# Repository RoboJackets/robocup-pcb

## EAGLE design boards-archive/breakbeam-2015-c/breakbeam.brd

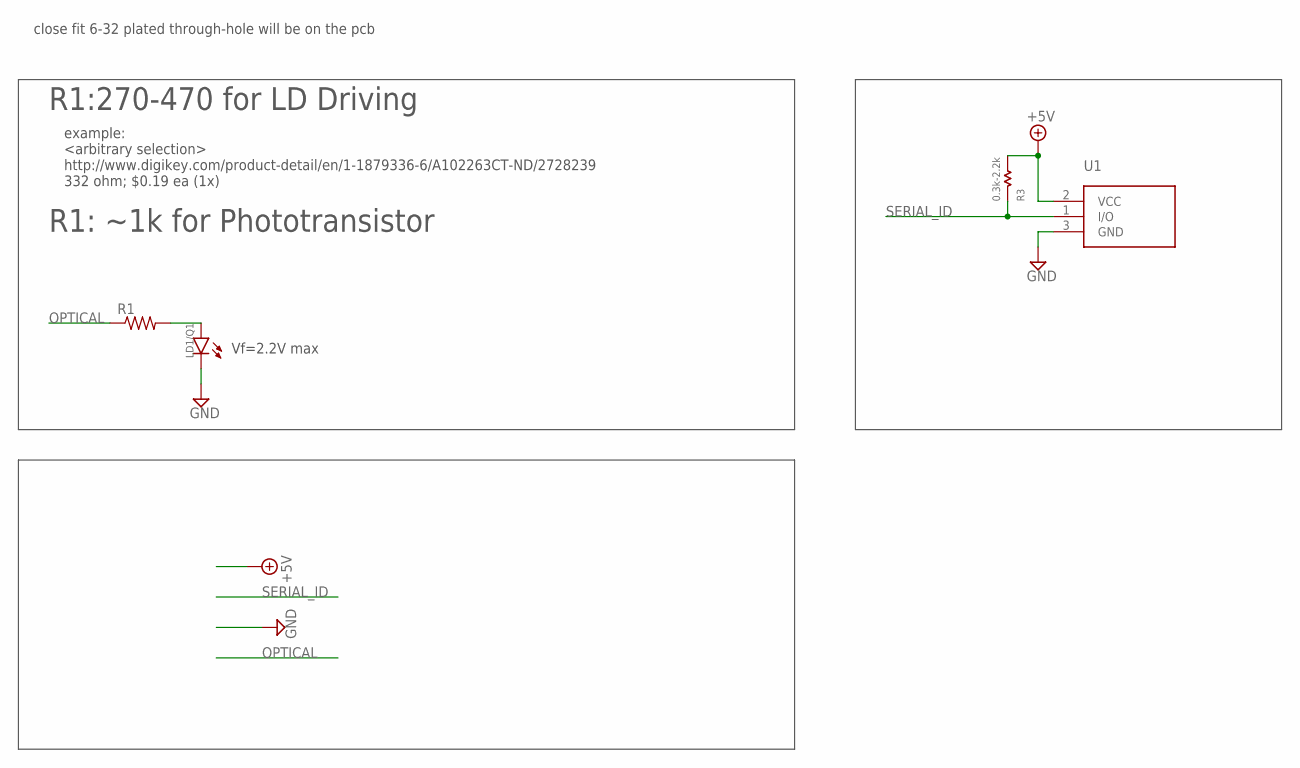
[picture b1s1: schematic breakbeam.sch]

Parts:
LD1/Q1: LD_SIDELOOK_FACEDOWNEXTRA_SHORT_LEAD_MINIMIZED; 2LEAD_H_FACEDOWN_XSHORT_MIN
R1: R-US_R0603; R0603
R3: 0.3k-2.2k; GHOST_0.075
U1: DS2411; SOT-23-3

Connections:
+5V: R3.P$2 (PIN2), U1.2 (VCC)
GND: LD1/Q1.1 (C), U1.3 (GND)
unnamed: LD1/Q1.2 (A), R1.2
OPTICAL: R1.1
SERIAL_ID: R3.P$1 (PIN1), U1.1 (I/O)

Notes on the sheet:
Vf=2.2V max
example: <arbitrary selection> http://www.digikey.com/product-detail/en/1-1879336-6/A102263CT-ND/2728239 332 ohm; $0.19 ea (1x)
close fit 6-32 plated through-hole will be on the pcb
R1:270-470 for LD Driving
R1: ~1k for Phototransistor

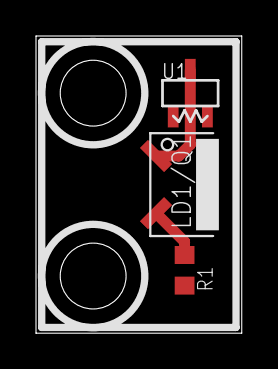
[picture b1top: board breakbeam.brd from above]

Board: 2 copper layers, 11.4 x 16.5 mm, 4 parts (0 on the bottom side), 4 nets.

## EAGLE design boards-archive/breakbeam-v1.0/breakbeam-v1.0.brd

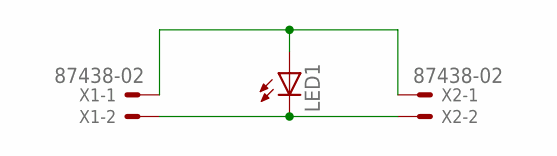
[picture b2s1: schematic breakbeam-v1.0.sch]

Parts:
LED1: LED3MM
X1, X2: 87438-02

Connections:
unnamed: LED1.A, X1.1, X2.1
unnamed: LED1.K (C), X1.2, X2.2

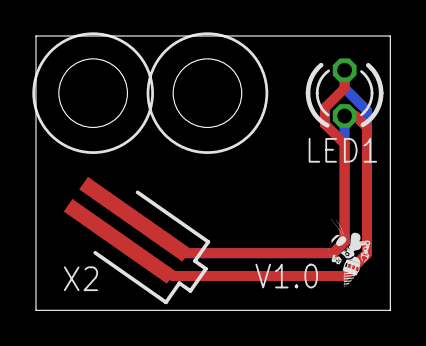
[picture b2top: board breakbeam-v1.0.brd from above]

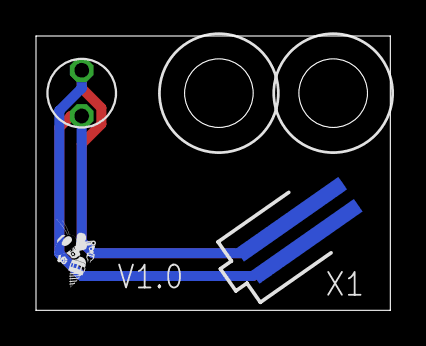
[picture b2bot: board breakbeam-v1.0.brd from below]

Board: 2 copper layers, 19.7 x 15.2 mm, 5 parts (2 on the bottom side), 2 nets.

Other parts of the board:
U$1, U$4: ROBOBUZZ_0.2X

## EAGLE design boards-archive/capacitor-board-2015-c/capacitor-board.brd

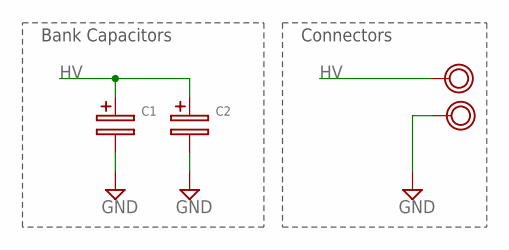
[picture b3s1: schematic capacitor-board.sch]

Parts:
C1, C2: RC_CAPHORIZ; 25MM-DIA_HORIZ
U$1, U$3: VIA_TP; VIA_2MM

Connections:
GND: C1.-, C2.-, U$3.P$1
HV: C1.+, C2.+, U$1.P$1

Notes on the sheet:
Bank Capacitors
Connectors

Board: 2 copper layers, 6 parts (1 on the bottom side), 2 nets, no tracks yet.

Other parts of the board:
U$2, U$4: ROBOBUZZ_0.4X

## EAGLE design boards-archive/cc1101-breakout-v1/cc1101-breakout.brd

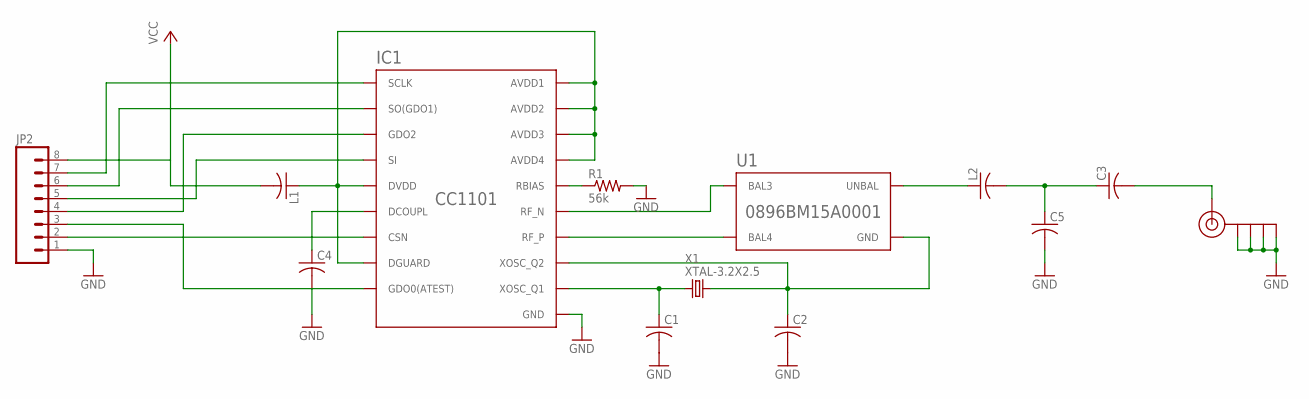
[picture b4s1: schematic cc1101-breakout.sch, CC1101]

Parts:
C1, C2, C3, C4: C-USC0603; C0603
C5: C-USC0402; C0402
IC1: CC1101; QLP20
J$1: SMA_EDGE; SMA-EDGE
JP2: M081X08; 1X08
L1: C-USC0603; C0603
L2: C-USC0402; C0402
R1: 56k; R0603
U1: 0896BM15A0001
X1: XTAL-3.2X2.5

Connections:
GND: C1.2, C2.2, C4.2, C5.2, IC1.16 (GND), IC1.19 (GND), IC1.GND, IC1.GND1 (GND), IC1.GND2 (GND), IC1.GND3 (GND), IC1.GND4 (GND), IC1.GND5 (GND), J$1.GND@0 (GND), J$1.GND@1 (GND), J$1.GND@2 (GND), J$1.GND@3 (GND), JP2.1, R1.2
unnamed: IC1.12 (RF_P), U1.4 (BAL4)
unnamed: IC1.13 (RF_N), U1.3 (BAL3)
unnamed: IC1.1 (SCLK), JP2.7
unnamed: C1.1, IC1.8 (XOSC_Q1), X1.1
unnamed: C2.1, IC1.10 (XOSC_Q2), U1.2 (GND), U1.5 (GND), U1.6 (GND), X1.3 (2)
unnamed: IC1.17 (RBIAS), R1.1
unnamed: IC1.2 (SO(GDO1)), JP2.6
unnamed: IC1.20 (SI), JP2.5
unnamed: L2.1, U1.1 (UNBAL)
unnamed: IC1.3 (GDO2), JP2.4
unnamed: IC1.6 (GDO0(ATEST)), JP2.3
unnamed: IC1.7 (CSN), JP2.2
unnamed: C4.1, IC1.5 (DCOUPL)
unnamed: C3.1, C5.1, L2.2
unnamed: C3.2, J$1.SIG (SIGNAL)
unnamed: IC1.4 (DVDD), IC1.9 (AVDD1), IC1.11 (AVDD2), IC1.14 (AVDD3), IC1.15 (AVDD4), IC1.18 (DGUARD), L1.1
VCC: JP2.8, L1.2

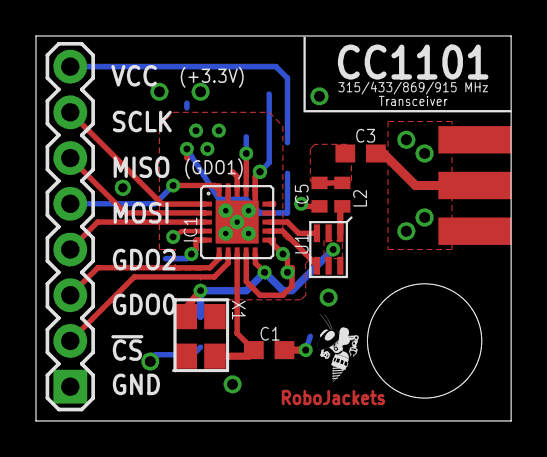
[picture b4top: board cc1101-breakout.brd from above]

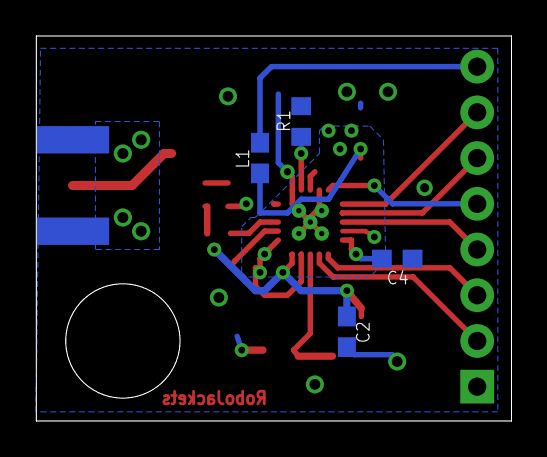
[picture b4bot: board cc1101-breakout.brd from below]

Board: 4 copper layers, 26.4 x 21.4 mm, 14 parts (4 on the bottom side), 18 nets.

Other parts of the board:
U$1: ROBOBUZZ_0.2X

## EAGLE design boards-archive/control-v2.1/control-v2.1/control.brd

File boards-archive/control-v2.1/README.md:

# Control Board

Board which contains micro-controller (MBED), power circuitry, FPGA, and all motor control circuitry.

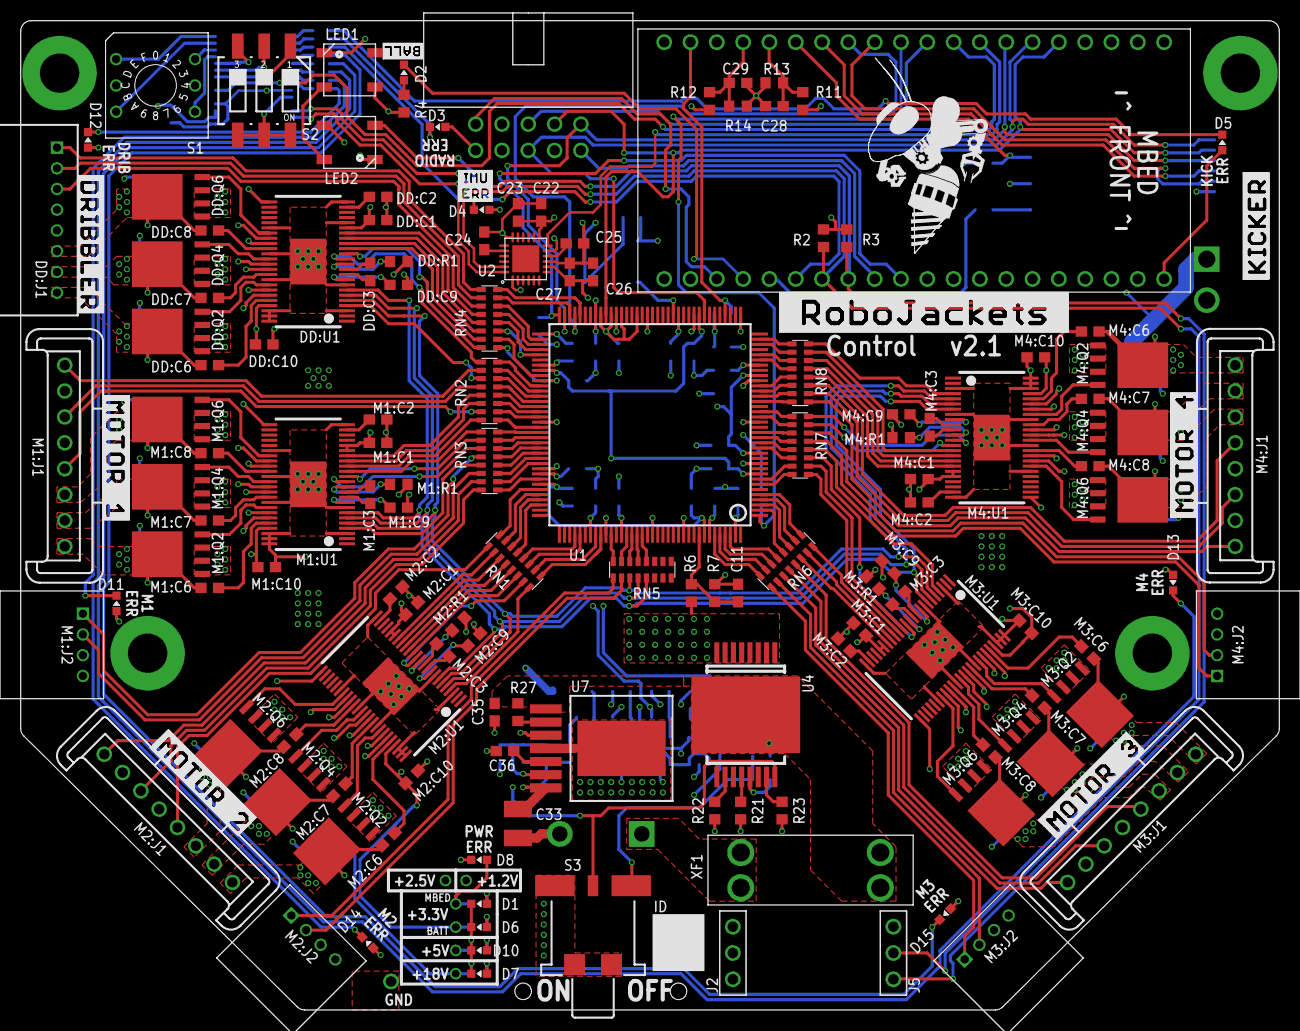
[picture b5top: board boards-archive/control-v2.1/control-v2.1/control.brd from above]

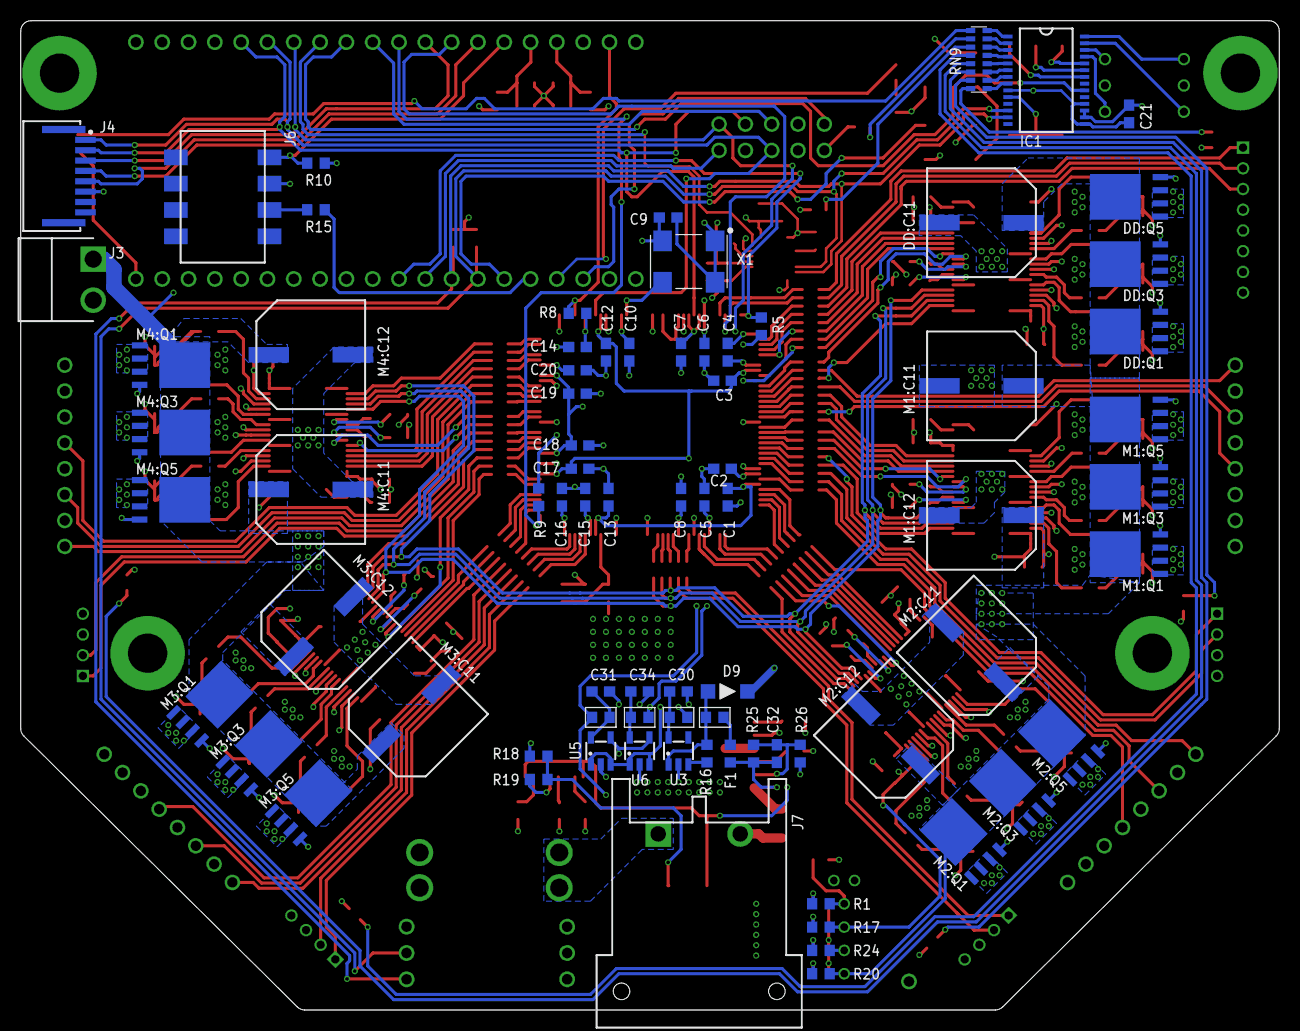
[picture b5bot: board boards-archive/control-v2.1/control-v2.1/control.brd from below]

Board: 4 copper layers, 121.5 x 95.5 mm, 223 parts (78 on the bottom side), 288 nets.

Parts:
C1, C2, C3, C4, C5, C6, C7, C8, C9, C10, C11, C12, C13, C14, C15, C16, C17, C18, C19, C20, C21, C25, C28, C29: 0.1uF; C0603
C22, C23, C27: 0.47uF; C0603
C24: 2200pF; C0603
C26: 10000pF; C0603
C30, C31, C34: 1uF; C0603
C32: 0.022uF; C0603
C33: LMK325ABJ107MM-P; C1210
C35: GRM188R6YA106MA73D; C0603
C36: 0.1uF 50V; C0603
D1, D6, D7, D10: GREEN; CHIP-LED0603
D2: BLUE; CHIP-LED0603
D3, D4, D5, D8, D11, D12, D13, D14, D15: RED; CHIP-LED0603
D9: SOD123
DD:C1, DD:C2: 1uF; C0603
DD:C3: 0.022uF 50V; C0603
DD:C6, DD:C7, DD:C8, DD:C10: 0.1uF 50V; C0603
DD:C9: 2.2uF 50V; C0603
DD:C11: UWZ1H221MCL1GS
DD:J1: 8-PIN_2MM-H; 2MM-8-H
DD:Q1, DD:Q2, DD:Q3, DD:Q4, DD:Q5, DD:Q6: IRFH7545; PQFN_5X6_E
DD:R1: 10k; R0603
DD:U1: DRV8303DCA; TSSOP-48_PAD
F1: 0603L075SLYR; F0603
IC1: MCP23017-E/SS; SSOP-28
J1: SBH11-PBPC-D05-RA; SBH11-*-D05-RA
J2, J5: 3-PIN-HEADER
J3: B2PS-VH(LF)(SN); B2PS-CENTERED
J4: HFW8R-1ST
J6: 147721-3
J7: DF22-2; DF22-2-H
KIT1: MBED_NXP_LPC1768; MBED-KIT
LED1, LED2: WS2812B; 5050
M1:C1, M1:C2, M2:C1, M2:C2, M3:C1, M3:C2, M4:C1, M4:C2: 1uF; C0603
M1:C3, M2:C3, M3:C3, M4:C3: 0.022uF 50V; C0603
M1:C6, M1:C7, M1:C8, M1:C10, M2:C6, M2:C7, M2:C8, M2:C10, M3:C6, M3:C7, M3:C8, M3:C10, M4:C6, M4:C7, M4:C8, M4:C10: 0.1uF 50V; C0603
M1:C9, M2:C9, M3:C9, M4:C9: 2.2uF 50V; C0603
M1:C11, M1:C12, M2:C11, M2:C12, M3:C11, M3:C12, M4:C11, M4:C12: UWZ1H221MCL1GS
M1:J1, M2:J1, M3:J1, M4:J1: MKS-1658
M1:J2, M2:J2, M3:J2, M4:J2: 4-PIN_2MM-H; 2MM-4-H
M1:Q1, M1:Q2, M1:Q3, M1:Q4, M1:Q5, M1:Q6, M2:Q1, M2:Q2, M2:Q3, M2:Q4, M2:Q5, M2:Q6, M3:Q1, M3:Q2, M3:Q3, M3:Q4, M3:Q5, M3:Q6, M4:Q1, M4:Q2, M4:Q3, M4:Q4, M4:Q5, M4:Q6: IRFH7545; PQFN_5X6_E
M1:R1, M2:R1, M3:R1, M4:R1: 10k; R0603
M1:U1, M2:U1, M3:U1, M4:U1: DRV8303DCA; TSSOP-48_PAD
R1, R4, R5, R15, R17: 330; R0603
R2, R3, R8, R9: 4.7k; R0603
R6, R11: 68k; R0603
R7, R10, R12, R13, R14, R16, R21: 10k; R0603
R18: 270k; R0603
R19, R27: 100k; R0603
R20, R22, R23, R24: 1k; R0603
R25: 34k; R0603
R26: 6.49k; R0603
RN1, RN2, RN3, RN4, RN5, RN6, RN7, RN8, RN9: 330; RA-8_2506
S1: 94HCB16T; HEX
S2: 219-03; CTS-219-03
S3: 34EWMSP12M6RT
SB1, SB2, SB3, SB4: SOLDERBRIDGESB0603; SB0603
U1: XC3S250E-4TQG144C; TQFP144
U2: MPU-6050; QFN-24-4MM2
U3: TLV70233DBVR; SOT-23-5
U4: VND5E006ASPTR-E; POWERSO-16
U5: MCP1824T-1202E/OT; SOT-23-5
U6: MCP1824T-2502E/OT; SOT-23-5
U7: LMZ14201; TO-PMOD-7
U$2: ROBOJACKETS
U$3: MOTOR-1
U$4: DRIBBLER
U$5: MOTOR-2
U$6: MOTOR-3
U$7: MOTOR-4
U$8: BALL
U$9: KICKER
U$10: ERR-IMU
U$11: ROBOBUZZ_1.0X2
X1: ASV-18.432MHZ-EJ-T; ASV
XF1: 30A; 3557-2

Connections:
3.3V-EN: R16.1, U3.3
3V3-LED: D6.A, R17.1
5V-LED: D10.A, R24.2
18.5V-LED: D7.A, R20.1
!CS!-FPGA: KIT1.P$13, U1.69
!CS!-KICK: J4.4, KIT1.P$14
!CS!-RADIO: J1.10, KIT1.P$29
!RST!-KICK: J4.5, KIT1.P$12
!RST!-RADIO: J1.5, KIT1.P$23
+1.2V: C3.1, C5.1, C12.1, C17.1, SB2.2, U1.9, U1.45, U1.80, U1.115
+1.2V-PRE: C31.1, SB2.1, U5.5
+2.5V: C1.1, C6.1, C13.1, C20.1, R5.2, R9.2, SB4.2, U1.30, U1.65, U1.102, U1.137
+2.5V-PRE: C34.1, SB4.1, U6.5
+3.3V: C2.1, C4.1, C7.1, C8.1, C9.1, C10.1, C14.1, C15.1, C16.1, C18.1, C19.1, C21.1, C22.1, C23.1, C26.1, C27.1, D3.A, D4.A, D5.A, D8.A, D11.A, D12.A, D13.A, D14.A, D15.A, DD:J1.5, IC1.9, IC1.15, IC1.18, J1.6, J2.2, KIT1.VOUT, LED1.1, LED2.1, R1.1, R2.2, R3.2, R4.2, R8.1, R10.2, U1.13, U1.28, U1.42, U1.49, U1.57, U1.60, U1.62, U1.64, U1.79, U1.100, U1.121, U1.138, U1.143, U2.8, U2.13, U5.1, U5.3, U6.1, U6.3, X1.1, X1.4
+3.3V-LED: D1.A, R1.2
+3V3: DD:C1.1, DD:C10.1, DD:R1.1, DD:U1.19, DD:U1.45, M1:C1.1, M1:C10.1, M1:R1.1, M1:U1.19, M1:U1.20, M1:U1.45, M2:C1.1, M2:C10.1, M2:R1.1, M2:U1.19, M2:U1.20, M2:U1.45, M3:C1.1, M3:C10.1, M3:R1.1, M3:U1.19, M3:U1.20, M3:U1.45, M4:C1.1, M4:C10.1, M4:R1.1, M4:U1.19, M4:U1.20, M4:U1.45, R17.2, SB1.2
+3V3-PRE: C30.1, SB1.1, U3.5
+5V: D9.C, KIT1.VIN, KIT1.VU, M1:J1.4, M1:J2.4, M2:J1.4, M2:J2.4, M3:J1.4, M3:J2.4, M4:J1.4, M4:J2.4, R12.1, R24.1
+5V-FUSE: C32.1, C33.1, F1.1, R25.2, U7.7
+5V-PRE: D9.A, R16.2, SB3.2, U3.1
+5V-PRE2: F1.2, SB3.1
+18.5V: DD:C11.1, DD:Q1.5678, DD:Q3.5678, DD:Q5.5678, DD:U1.25, J3.1, M1:C11.1, M1:C12.1, M1:Q1.5678, M1:Q3.5678, M1:Q5.5678, M1:U1.25, M2:C11.1, M2:C12.1, M2:Q1.5678, M2:Q3.5678, M2:Q5.5678, M2:U1.25, M3:C11.1, M3:C12.1, M3:Q1.5678, M3:Q3.5678, M3:Q5.5678, M3:U1.25, M4:C11.1, M4:C12.1, M4:Q1.5678, M4:Q3.5678, M4:Q5.5678, M4:U1.25, R6.1, R11.1, R20.2, U4.1, U4.2, U4.3, U4.4, U4.5, U4.6, U4.7, U4.8
BALL-DETECT: J6.1, KIT1.P$15, R10.1
BALL-EMIT: KIT1.P$25, R15.2
BALL-EMIT-PRE: J6.3, R15.1
BATT-FPGA: C11.1, R6.2, R7.1, U1.136
CPOUT: C24.1, U2.20
CS1: R22.2, U4.10
CS2: R23.2, U4.15
CS-DIS: R21.2, U4.12
DD-!CS: DD:U1.4, RN2.11
DD-A-H: DD:U1.13, RN2.9
DD-A-L: DD:U1.14, RN4.16
DD-B-H: DD:U1.15, RN4.15
DD-B-L: DD:U1.16, RN4.14
DD-C-H: DD:U1.17, RN4.13
DD-C-L: DD:U1.18, RN4.12
DD-H1: DD:J1.3, RN4.11
DD-H2: DD:J1.2, RN4.10
DD-H3: DD:J1.1, RN4.9
DD:AVDD: DD:C2.1, DD:U1.23
DD:BST-A: DD:C6.1, DD:U1.44
DD:BST-B: DD:C7.1, DD:U1.39
DD:BST-C: DD:C8.1, DD:U1.34
DD:CP1: DD:C3.1, DD:U1.10
DD:CP2: DD:C3.2, DD:U1.11
DD:EN-GATE: DD:R1.2, DD:U1.12
DD:GH-A: DD:Q1.4, DD:U1.43
DD:GH-B: DD:Q3.4, DD:U1.38
DD:GH-C: DD:Q5.4, DD:U1.33
DD:GL-A: DD:Q2.4, DD:U1.41
DD:GL-B: DD:Q4.4, DD:U1.36
DD:GL-C: DD:Q6.4, DD:U1.31
DD:GVDD: DD:C9.1, DD:U1.9
DD:PHASE-A: DD:C6.2, DD:J1.8, DD:Q1.1, DD:Q1.2, DD:Q1.3, DD:Q2.5678, DD:U1.42
DD:PHASE-B: DD:C7.2, DD:J1.7, DD:Q3.1, DD:Q3.2, DD:Q3.3, DD:Q4.5678, DD:U1.37
DD:PHASE-C: DD:C8.2, DD:J1.6, DD:Q5.1, DD:Q5.2, DD:Q5.3, DD:Q6.5678, DD:U1.32
DIP-1: IC1.22, S2.1
DIP-2: IC1.23, S2.2
DIP-3: IC1.24, S2.3
EN-PWR: S3.2, U4.9, U4.16, U7.3
EN-PWR-PRE: R18.1, R19.2, S3.1
FB: C32.2, R25.1, R26.2, U7.6
FPGA-CLK: U1.50, X1.3
FPGA-DONE: KIT1.P$30, R5.1, U1.72
FPGA-INIT: KIT1.P$19, R8.2, U1.40
FPGA-PROG: KIT1.P$11, R9.1, U1.1
GND: C1.2, C2.2, C3.2, C4.2, C5.2, C6.2, C7.2, C8.2, C9.2, C10.2, C11.2, C12.2, C13.2, C14.2, C15.2, C16.2, C17.2, C18.2, C19.2, C20.2, C21.2, C22.2, C23.2, C24.2, C25.2, C26.2, C27.2, C28.2, C29.2, C30.2, C31.2, C33.2, C34.2, C35.2, C36.2, D1.C, D6.C, D7.C, D10.C, DD:C1.2, DD:C2.2, DD:C9.2, DD:C10.2, DD:C11.2, DD:J1.4, DD:Q2.1, DD:Q2.2, DD:Q2.3, DD:Q4.1, DD:Q4.2, DD:Q4.3, DD:Q6.1, DD:Q6.2, DD:Q6.3, DD:U1.3, DD:U1.8, DD:U1.20, DD:U1.24, DD:U1.30, DD:U1.35, DD:U1.40, DD:U1.46, DD:U1.47, DD:U1.48, DD:U1.PAD, IC1.10, IC1.16, IC1.17, J1.7, J2.1, J3.2, J4.6, J6.2, J7.2, KIT1.GND, LED1.3, LED2.3, M1:C1.2, M1:C2.2, M1:C9.2, M1:C10.2, M1:C11.2, M1:C12.2, M1:J1.2, M1:J2.3, M1:Q2.1, M1:Q2.2, M1:Q2.3, M1:Q4.1, M1:Q4.2, M1:Q4.3, M1:Q6.1, M1:Q6.2, M1:Q6.3, M1:U1.3, M1:U1.8, M1:U1.24, M1:U1.30, M1:U1.35, M1:U1.40, M1:U1.46, M1:U1.47, M1:U1.48, M1:U1.PAD, M2:C1.2, M2:C2.2, M2:C9.2, M2:C10.2, M2:C11.2, M2:C12.2, M2:J1.2, M2:J2.3, M2:Q2.1, M2:Q2.2, M2:Q2.3, M2:Q4.1, M2:Q4.2, M2:Q4.3, M2:Q6.1, M2:Q6.2, M2:Q6.3, M2:U1.3, M2:U1.8, M2:U1.24, M2:U1.30, M2:U1.35, M2:U1.40, M2:U1.46, M2:U1.47, M2:U1.48, M2:U1.PAD, M3:C1.2, M3:C2.2, M3:C9.2, M3:C10.2, M3:C11.2, M3:C12.2, M3:J1.2, M3:J2.3, M3:Q2.1, M3:Q2.2, M3:Q2.3, M3:Q4.1, M3:Q4.2, M3:Q4.3, M3:Q6.1, M3:Q6.2, M3:Q6.3, M3:U1.3, M3:U1.8, M3:U1.24, M3:U1.30, M3:U1.35, M3:U1.40, M3:U1.46, M3:U1.47, M3:U1.48, M3:U1.PAD, M4:C1.2, M4:C2.2, M4:C9.2, M4:C10.2, M4:C11.2, M4:C12.2, M4:J1.2, M4:J2.3, M4:Q2.1, M4:Q2.2, M4:Q2.3, M4:Q4.1, M4:Q4.2, M4:Q4.3, M4:Q6.1, M4:Q6.2, M4:Q6.3, M4:U1.3, M4:U1.8, M4:U1.24, M4:U1.30, M4:U1.35, M4:U1.40, M4:U1.46, M4:U1.47, M4:U1.48, M4:U1.PAD, R7.2, R13.2, R14.2, R19.1, R21.1, R22.1, R23.1, R26.1, S1.C1, S1.C2, S2.4, S2.5, S2.6, S3.3, S3.LEG1, S3.LEG3, U1.11, U1.19, U1.27, U1.37, U1.46, U1.55, U1.61, U1.73, U1.90, U1.99, U1.118, U1.127, U1.133, U2.1, U2.9, U2.11, U2.18, U3.2, U4.13, U5.2, U6.2, U7.4, U7.PAD, X1.2
GPB0: IC1.1, RN9.8
GPB1: IC1.2, RN9.7
GPB2: IC1.3, RN9.6
GPB3: IC1.4, RN9.5
GPB4: IC1.5, RN9.4
GPB5: IC1.6, RN9.3
GPB6: IC1.7, RN9.2
GPB7: IC1.8, RN9.1
HEX-0: IC1.28, S1.1
HEX-1: IC1.25, S1.2
HEX-2: IC1.27, S1.4
HEX-3: IC1.26, S1.8
INT-IO: IC1.20, KIT1.P$9
INT-MPU: KIT1.P$8, U2.12
INT-RADIO: J1.3, KIT1.P$10
LED-BALL: D2.C, KIT1.P$24
LED-BALL-PRE: D2.A, R4.1
LED-DD: D12.C, RN9.16
LED-KICK: D5.C, RN9.9
LED-M1: D11.C, RN9.15
LED-M2: D14.C, RN9.14
LED-M3: D15.C, RN9.12
LED-M4: D13.C, RN9.13
LED-MPU: D4.C, RN9.11
LED-NEO: KIT1.P$26, LED2.4
LED-RADIO: D3.C, RN9.10
M1-!CS: M1:U1.4, RN3.13
M1-A-H: M1:U1.15, RN3.9
M1-A-L: M1:U1.16, RN2.16
M1-B-H: M1:U1.13, RN3.11
M1-B-L: M1:U1.14, RN3.10
M1-C-H: M1:U1.17, RN2.14
M1-C-L: M1:U1.18, RN2.13
M1-ENC-A: M1:J2.2, RN3.14
M1-ENC-B: M1:J2.1, RN3.12
M1-H1: M1:J1.1, RN2.10
M1-H2: M1:J1.3, RN2.12
M1-H3: M1:J1.5, RN2.15
M1:AVDD: M1:C2.1, M1:U1.23
M1:BST-A: M1:C6.1, M1:U1.44
M1:BST-B: M1:C7.1, M1:U1.39
M1:BST-C: M1:C8.1, M1:U1.34
M1:CP1: M1:C3.1, M1:U1.10
M1:CP2: M1:C3.2, M1:U1.11
M1:EN-GATE: M1:R1.2, M1:U1.12
M1:GH-A: M1:Q1.4, M1:U1.43
M1:GH-B: M1:Q3.4, M1:U1.38
M1:GH-C: M1:Q5.4, M1:U1.33
M1:GL-A: M1:Q2.4, M1:U1.41
M1:GL-B: M1:Q4.4, M1:U1.36
M1:GL-C: M1:Q6.4, M1:U1.31
M1:GVDD: M1:C9.1, M1:U1.9
M1:PHASE-A: M1:C7.2, M1:J1.7, M1:Q3.1, M1:Q3.2, M1:Q3.3, M1:Q4.5678, M1:U1.37
M1:PHASE-B: M1:C6.2, M1:J1.8, M1:Q1.1, M1:Q1.2, M1:Q1.3, M1:Q2.5678, M1:U1.42
M1:PHASE-C: M1:C8.2, M1:J1.6, M1:Q5.1, M1:Q5.2, M1:Q5.3, M1:Q6.5678, M1:U1.32
M2-!CS: M2:U1.4, RN1.16
M2-A-H: M2:U1.15, RN1.13
M2-A-L: M2:U1.16, RN1.12
M2-B-H: M2:U1.13, RN1.15
M2-B-L: M2:U1.14, RN1.14
M2-C-H: M2:U1.17, RN1.11
M2-C-L: M2:U1.18, RN1.10
M2-ENC-A: M2:J2.2, RN5.10
M2-ENC-B: M2:J2.1, RN5.9
M2-H1: M2:J1.1, RN3.15
M2-H2: M2:J1.3, RN3.16
M2-H3: M2:J1.5, RN1.9
M2:AVDD: M2:C2.1, M2:U1.23
M2:BST-A: M2:C6.1, M2:U1.44
M2:BST-B: M2:C7.1, M2:U1.39
M2:BST-C: M2:C8.1, M2:U1.34
M2:CP1: M2:C3.1, M2:U1.10
M2:CP2: M2:C3.2, M2:U1.11
M2:EN-GATE: M2:R1.2, M2:U1.12
M2:GH-A: M2:Q1.4, M2:U1.43
M2:GH-B: M2:Q3.4, M2:U1.38
M2:GH-C: M2:Q5.4, M2:U1.33
M2:GL-A: M2:Q2.4, M2:U1.41
M2:GL-B: M2:Q4.4, M2:U1.36
M2:GL-C: M2:Q6.4, M2:U1.31
M2:GVDD: M2:C9.1, M2:U1.9
M2:PHASE-A: M2:C7.2, M2:J1.7, M2:Q3.1, M2:Q3.2, M2:Q3.3, M2:Q4.5678, M2:U1.37
M2:PHASE-B: M2:C6.2, M2:J1.8, M2:Q1.1, M2:Q1.2, M2:Q1.3, M2:Q2.5678, M2:U1.42
M2:PHASE-C: M2:C8.2, M2:J1.6, M2:Q5.1, M2:Q5.2, M2:Q5.3, M2:Q6.5678, M2:U1.32
M3-!CS: M3:U1.4, RN7.12
M3-A-H: M3:U1.15, RN7.9
M3-A-L: M3:U1.16, RN6.16
M3-B-H: M3:U1.13, RN7.11
M3-B-L: M3:U1.14, RN7.10
M3-C-H: M3:U1.17, RN6.15
M3-C-L: M3:U1.18, RN6.14
M3-ENC-A: M3:J2.2, RN6.10
M3-ENC-B: M3:J2.1, RN6.9
M3-H1: M3:J1.1, RN6.11
M3-H2: M3:J1.3, RN6.12
M3-H3: M3:J1.5, RN6.13
M3:AVDD: M3:C2.1, M3:U1.23
M3:BST-A: M3:C6.1, M3:U1.44
M3:BST-B: M3:C7.1, M3:U1.39
M3:BST-C: M3:C8.1, M3:U1.34
M3:CP1: M3:C3.1, M3:U1.10
M3:CP2: M3:C3.2, M3:U1.11
M3:EN-GATE: M3:R1.2, M3:U1.12
M3:GH-A: M3:Q1.4, M3:U1.43
M3:GH-B: M3:Q3.4, M3:U1.38
M3:GH-C: M3:Q5.4, M3:U1.33
M3:GL-A: M3:Q2.4, M3:U1.41
M3:GL-B: M3:Q4.4, M3:U1.36
M3:GL-C: M3:Q6.4, M3:U1.31
M3:GVDD: M3:C9.1, M3:U1.9
M3:PHASE-A: M3:C7.2, M3:J1.7, M3:Q3.1, M3:Q3.2, M3:Q3.3, M3:Q4.5678, M3:U1.37
M3:PHASE-B: M3:C6.2, M3:J1.8, M3:Q1.1, M3:Q1.2, M3:Q1.3, M3:Q2.5678, M3:U1.42
M3:PHASE-C: M3:C8.2, M3:J1.6, M3:Q5.1, M3:Q5.2, M3:Q5.3, M3:Q6.5678, M3:U1.32
M4-!CS: M4:U1.4, RN8.16
M4-A-H: M4:U1.15, RN8.15
M4-A-L: M4:U1.16, RN8.14
M4-B-H: M4:U1.13, RN7.16
M4-B-L: M4:U1.14, RN7.15
M4-C-H: M4:U1.17, RN8.13
M4-C-L: M4:U1.18, RN8.12
M4-ENC-A: M4:J2.2, RN7.14
M4-ENC-B: M4:J2.1, RN7.13
M4-H1: M4:J1.1, RN8.9
M4-H2: M4:J1.3, RN8.10
M4-H3: M4:J1.5, RN8.11
M4:AVDD: M4:C2.1, M4:U1.23
M4:BST-A: M4:C6.1, M4:U1.44
M4:BST-B: M4:C7.1, M4:U1.39
M4:BST-C: M4:C8.1, M4:U1.34
M4:CP1: M4:C3.1, M4:U1.10
M4:CP2: M4:C3.2, M4:U1.11
M4:EN-GATE: M4:R1.2, M4:U1.12
M4:GH-A: M4:Q1.4, M4:U1.43
M4:GH-B: M4:Q3.4, M4:U1.38
M4:GH-C: M4:Q5.4, M4:U1.33
M4:GL-A: M4:Q2.4, M4:U1.41
M4:GL-B: M4:Q4.4, M4:U1.36
M4:GL-C: M4:Q6.4, M4:U1.31
M4:GVDD: M4:C9.1, M4:U1.9
M4:PHASE-A: M4:C7.2, M4:J1.7, M4:Q3.1, M4:Q3.2, M4:Q3.3, M4:Q4.5678, M4:U1.37
M4:PHASE-B: M4:C6.2, M4:J1.8, M4:Q1.1, M4:Q1.2, M4:Q1.3, M4:Q2.5678, M4:U1.42
M4:PHASE-C: M4:C8.2, M4:J1.6, M4:Q5.1, M4:Q5.2, M4:Q5.3, M4:Q6.5678, M4:U1.32
MISO: J1.8, J4.1, KIT1.P$6, U1.44
MISO-AUX: DD:U1.6, M1:U1.6, M2:U1.6, M3:U1.6, M4:U1.6, RN5.12
MOSI: J1.2, J4.2, KIT1.P$5, U1.63
MOSI-AUX: DD:U1.5, M1:U1.5, M2:U1.5, M3:U1.5, M4:U1.5, RN5.11
NEO-IO: LED1.4, LED2.2
PWR-ERR: D8.C, U5.4, U6.4
R-P1: RN4.1, U1.82
R-P2: RN4.2, U1.81
R-P3: RN4.3, U1.77
R-P4: RN4.4, U1.76
R-P5: RN4.5, U1.75
R-P6: RN4.6, U1.74
R-P7: RN4.7, U1.70
R-P8: RN4.8, U1.68
R-P9: RN2.1, U1.91
R-P10: RN2.2, U1.89
R-P11: RN2.3, U1.88
R-P12: RN2.4, U1.87
R-P13: RN2.5, U1.86
R-P14: RN2.6, U1.85
R-P15: RN2.7, U1.84
R-P16: RN2.8, U1.83
R-P17: RN3.1, U1.101
R-P18: RN3.2, U1.98
R-P19: RN3.3, U1.97
R-P20: RN3.4, U1.96
R-P21: RN3.5, U1.95
R-P22: RN3.6, U1.94
R-P23: RN3.7, U1.93
R-P24: RN3.8, U1.92
R-P25: RN1.1, U1.117
R-P26: RN1.2, U1.116
R-P27: RN1.3, U1.113
R-P28: RN1.4, U1.112
R-P29: RN1.5, U1.106
R-P30: RN1.6, U1.105
R-P31: RN1.7, U1.104
R-P32: RN1.8, U1.103
R-P36: RN5.4, U1.125
R-P37: RN5.5, U1.124
R-P38: RN5.6, U1.123
R-P39: RN5.7, U1.122
R-P40: RN5.8, U1.119
R-P41: RN6.1, U1.5
R-P42: RN6.2, U1.4
R-P43: RN6.3, U1.3
R-P44: RN6.4, U1.2
R-P45: RN6.5, U1.142
R-P46: RN6.6, U1.141
R-P47: RN6.7, U1.140
R-P48: RN6.8, U1.139
R-P49: RN7.1, U1.21
R-P50: RN7.2, U1.20
R-P51: RN7.3, U1.17
R-P52: RN7.4, U1.16
R-P53: RN7.5, U1.15
R-P54: RN7.6, U1.14
R-P55: RN7.7, U1.8
R-P56: RN7.8, U1.7
R-P57: RN8.1, U1.35
R-P58: RN8.2, U1.34
R-P59: RN8.3, U1.32
R-P60: RN8.4, U1.31
R-P61: RN8.5, U1.26
R-P62: RN8.6, U1.25
R-P63: RN8.7, U1.24
R-P64: RN8.8, U1.23
REGOUT: C25.1, U2.10
RON: R27.2, U7.2
SCK: J1.1, J4.3, KIT1.P$7, U1.71
SCK-AUX: DD:U1.7, M1:U1.7, M2:U1.7, M3:U1.7, M4:U1.7, RN5.13
SCL: IC1.12, J5.2, KIT1.P$27, R2.1, U2.23
SDA: IC1.13, J5.1, KIT1.P$28, R3.1, U2.24
SENSE-BATT: C28.1, KIT1.P$16, R11.2, R13.1
SENSE-VIN: C29.1, KIT1.P$17, R12.2, R14.1
SS: C36.1, U7.5
VBATT: C35.1, R18.2, R27.1, U4.17, U7.1, XF1.3, XF1.4
VIN: J7.1, XF1.1, XF1.2

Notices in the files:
parts and their libraries:
SparkFun-Connectors: Licensing: Creative Commons ShareAlike 4.0 International - https://creativecommons.org/licenses/by-sa/4.0
